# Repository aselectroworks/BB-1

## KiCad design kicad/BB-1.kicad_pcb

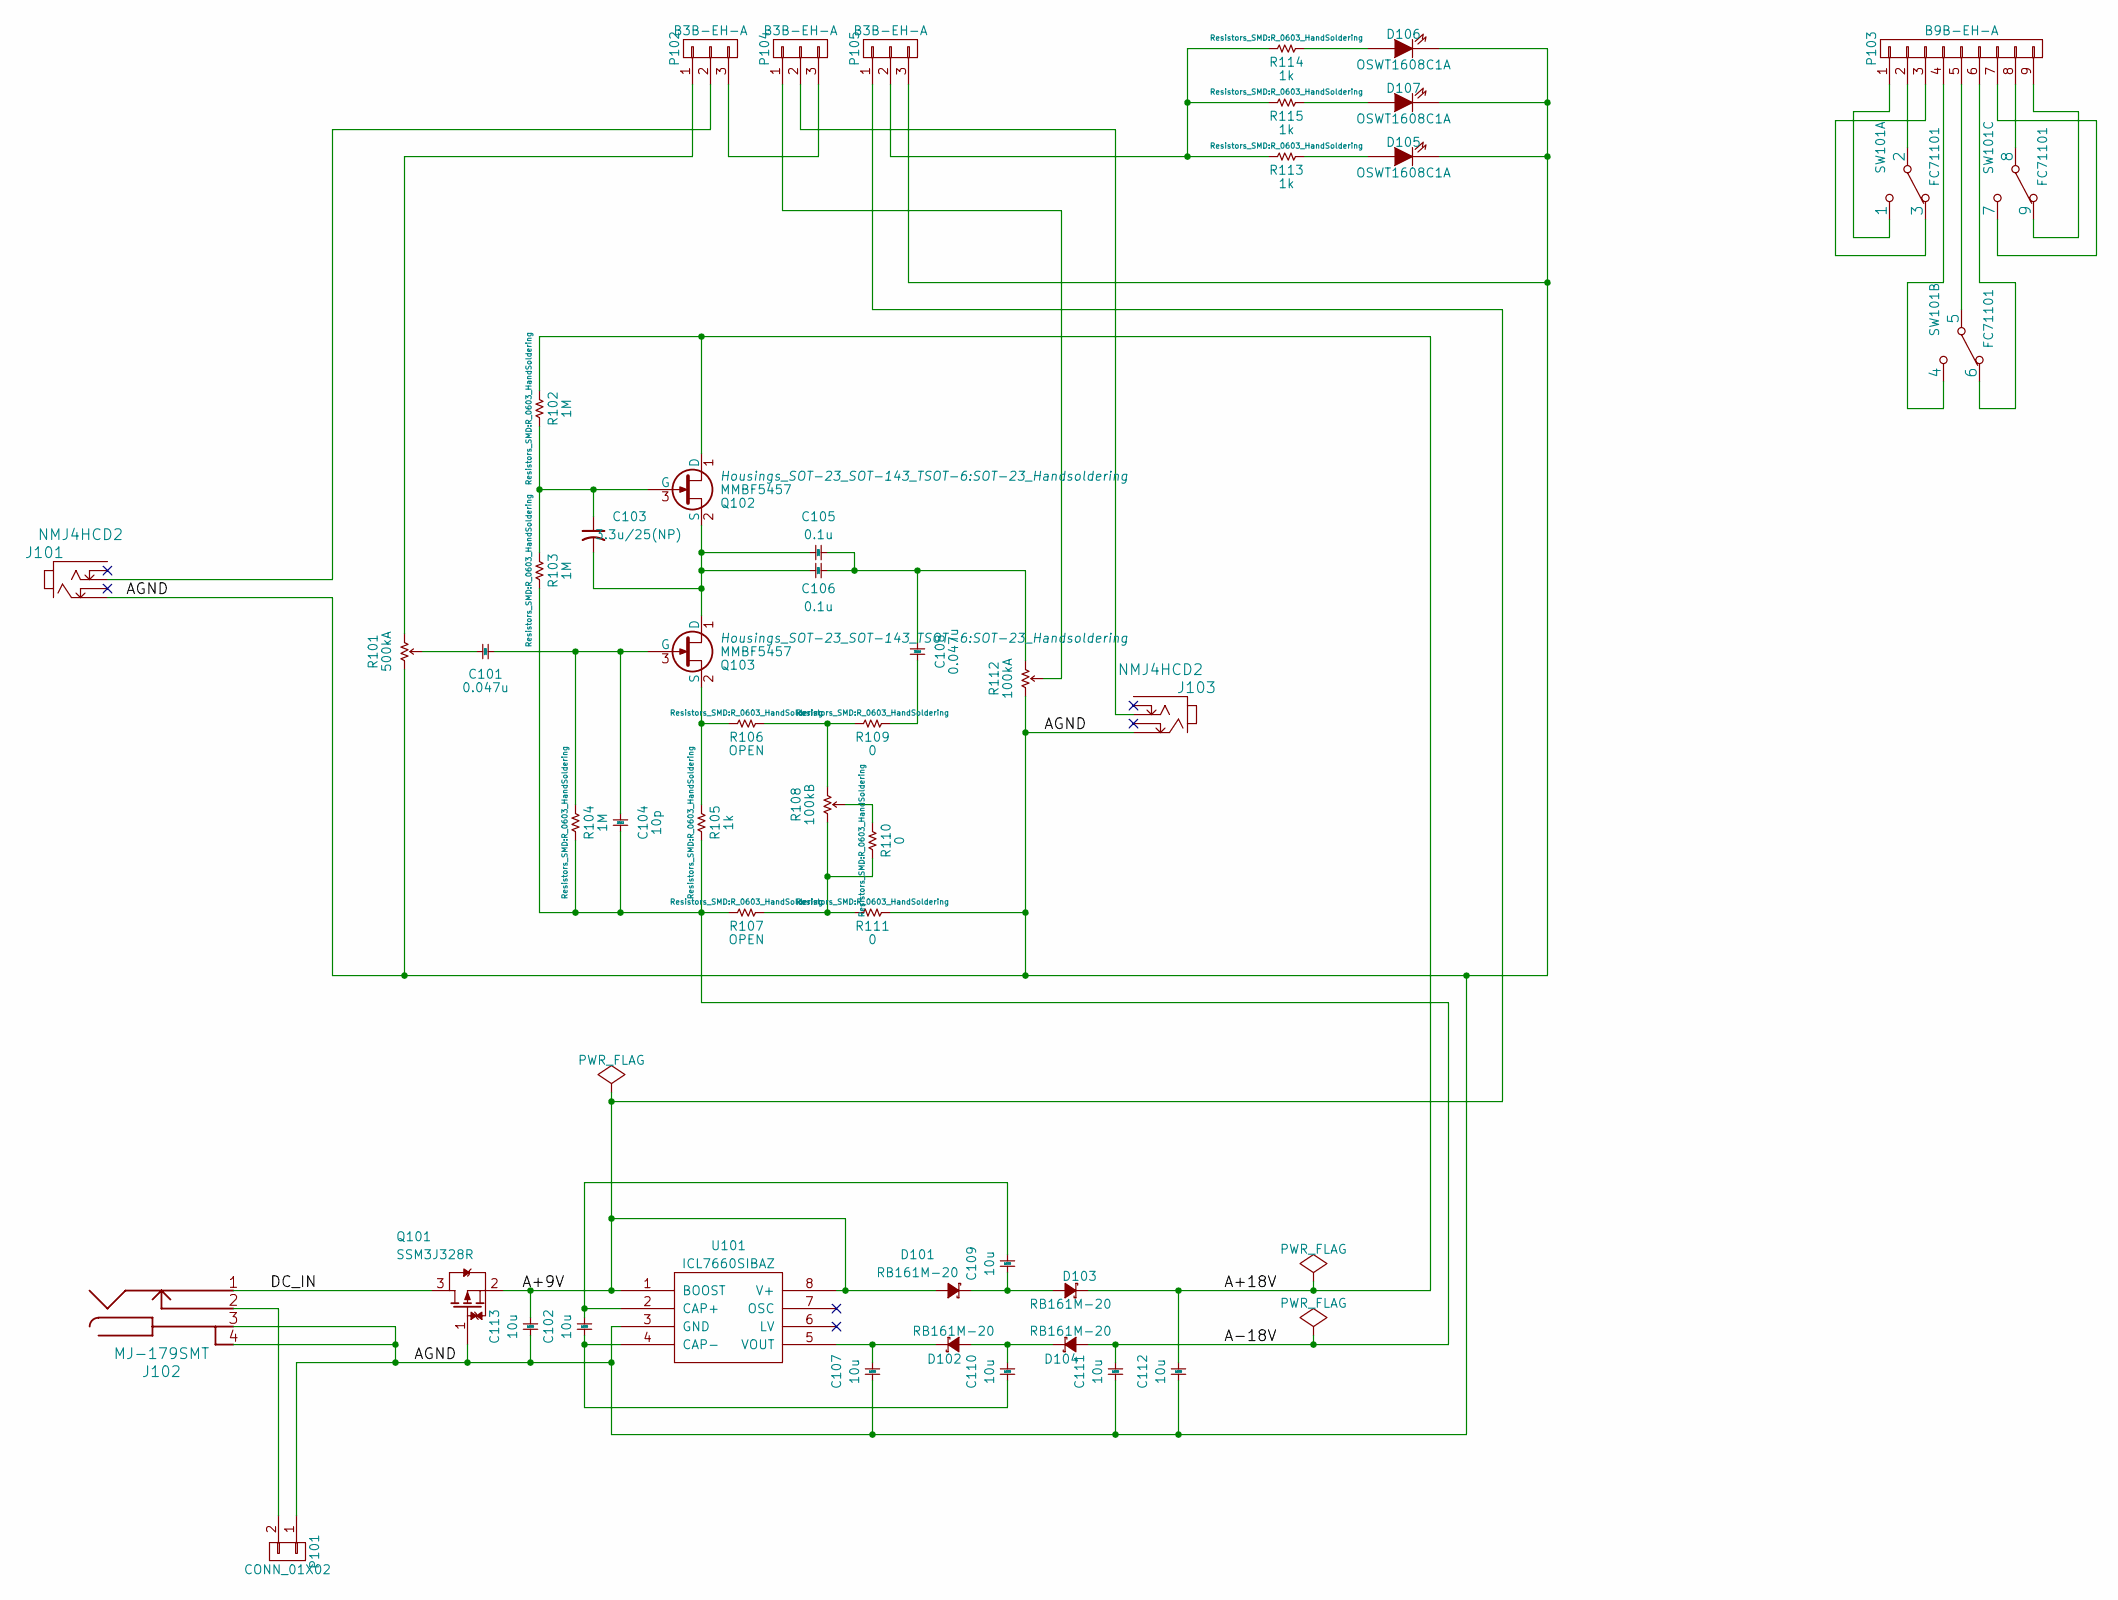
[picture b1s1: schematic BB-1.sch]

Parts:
C101, C108: GRM31M5C1H473JA01L; C_1206_HandSoldering
C102, C107, C109, C110, C111, C112, C113: GRM188R60J106ME47J; C_0603_HandSoldering
C103: EEE1EA3R3NR; c_elec_4x4.5
C104: GRM21A5C2E100JW01D; C_0805_HandSoldering
C105, C106: GRM31C5C1E104JA01L; C_1206_HandSoldering
D101, D102, D103, D104: RB161M-20; PMDU
D105, D106, D107: OSWT1608C1A; C_0603_HandSoldering
J101, J103: NMJ4HCD2
J102: MJ-179SMT
P101: CONN_01X02; Pin_Header_Straight_1x02
P102, P104, P105: B3B-EH-A
P103: B9B-EH-A
Q101: SSM3J328R; SOT-23_Handsoldering
Q102, Q103: MMBF5457; SOT-23_Handsoldering
R101: RV141F-40E3-18BL-A500K; RV141F-40E3
R102, R103, R104: MCR03ERTF1004; R_0603_HandSoldering
R105, R113, R114, R115: MCR03ERTF1001; R_0603_HandSoldering
R106, R107: MCR03ERTF; R_0603_HandSoldering
R108: RV141F-40E3-18BL-B100K; RV141F-40E3
R109, R110, R111: MCR03EZPJ000; R_0603_HandSoldering
R112: RV141F-40E3-18BL-A100K; RV141F-40E3
SW101: FC71101
U101: ICL7660SIBAZ; SOIC-8_3.9x4.9mm_Pitch1.27mm

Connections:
/A+9V: C113.1, D101.1 (A), P105.1, Q101.2 (S), U101.1 (BOOST), U101.8 (V+)
/A+18V: C112.1, D103.2 (C), Q102.1 (D), R102.2
/A-18V: C104.2, C111.1, D104.1 (A), R103.1, R104.1, R105.1, R107.1
/AGND: C107.2, C111.2, C112.2, C113.2, D105.1 (K), D106.1 (K), D107.1 (K), J101.S, J102.3, J102.4, J103.S, P101.1, P105.3, Q101.1 (G), R101.1, R111.2, R112.1, U101.3 (GND)
/DC_IN: J102.1, Q101.3 (D)
unnamed: C101.1, C104.1, Q103.3 (G), R104.2
unnamed: C101.2, R101.2
unnamed: C102.1, C109.1, U101.2 (CAP+)
unnamed: C102.2, C110.2, U101.4 (CAP-)
unnamed: C103.1, Q102.3 (G), R102.1, R103.2
unnamed: C103.2, C105.2, C106.2, Q102.2 (S), Q103.1 (D)
unnamed: C105.1, C106.1, C108.1, R112.3
unnamed: C107.1, D102.2 (C), U101.5 (VOUT)
unnamed: C108.2, R109.2
unnamed: C109.2, D101.2 (C), D103.1 (A)
unnamed: C110.1, D102.1 (A), D104.2 (C)
unnamed: D105.2 (A), R113.2
unnamed: D106.2 (A), R114.2
unnamed: D107.2 (A), R115.2
unnamed: J101.T, P102.2
unnamed: J102.2, P101.2
unnamed: J103.T, P104.2
unnamed: P102.1, R101.3
unnamed: P102.3, P104.3
unnamed: P103.1, SW101.1
unnamed: P103.2, SW101.2
unnamed: P103.3, SW101.3
unnamed: P103.4, SW101.4
unnamed: P103.5, SW101.5
unnamed: P103.6, SW101.6
unnamed: P103.7, SW101.7
unnamed: P103.8, SW101.8
unnamed: P103.9, SW101.9
unnamed: P104.1, R112.2
unnamed: P105.2, R113.1, R114.1, R115.1
unnamed: Q103.2 (S), R105.2, R106.1
unnamed: R106.2, R108.3, R109.1
unnamed: R107.2, R108.1, R110.1, R111.1
unnamed: R108.2, R110.2

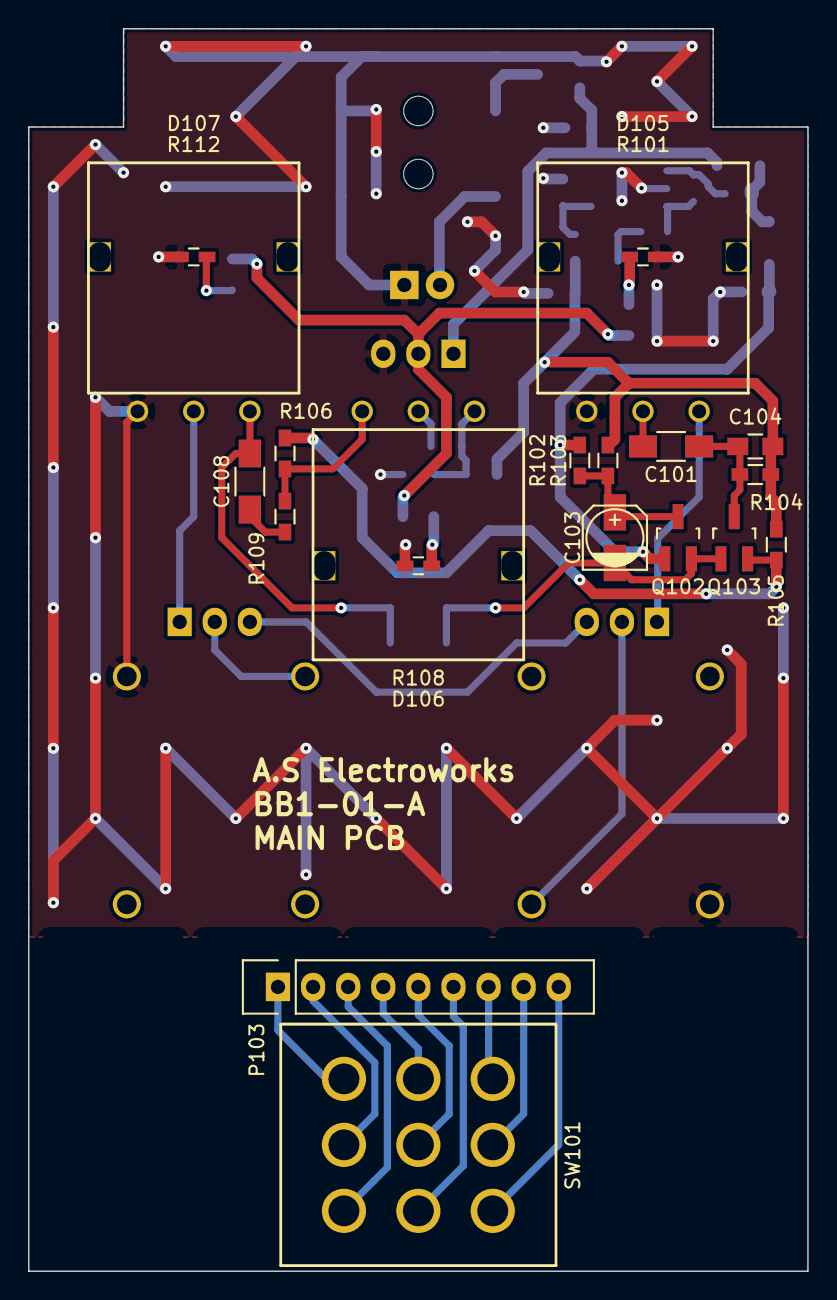
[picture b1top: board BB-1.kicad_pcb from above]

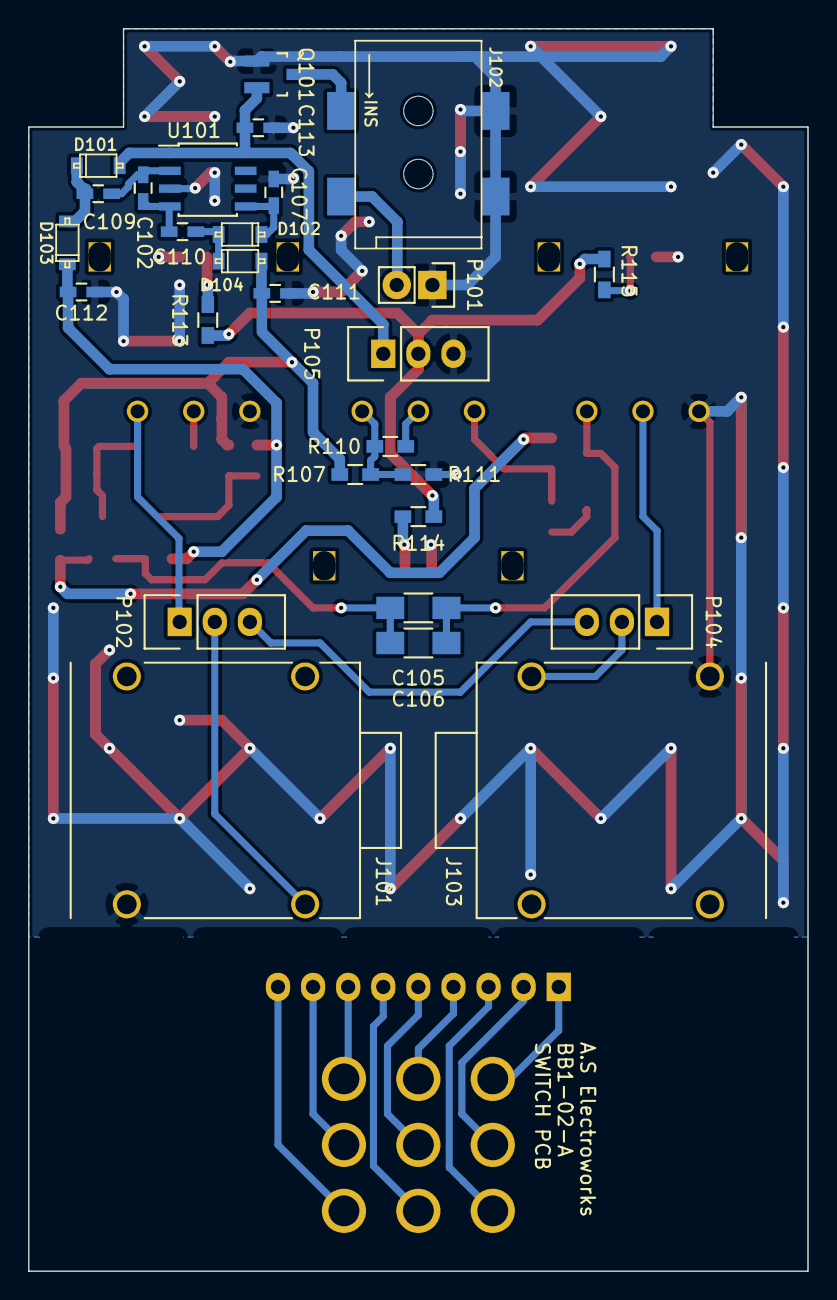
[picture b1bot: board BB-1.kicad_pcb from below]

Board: 2 copper layers, 55.5 x 88.5 mm, 48 parts (28 on the bottom side), 39 nets.

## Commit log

2015-07-01 ES1 CADOUT
